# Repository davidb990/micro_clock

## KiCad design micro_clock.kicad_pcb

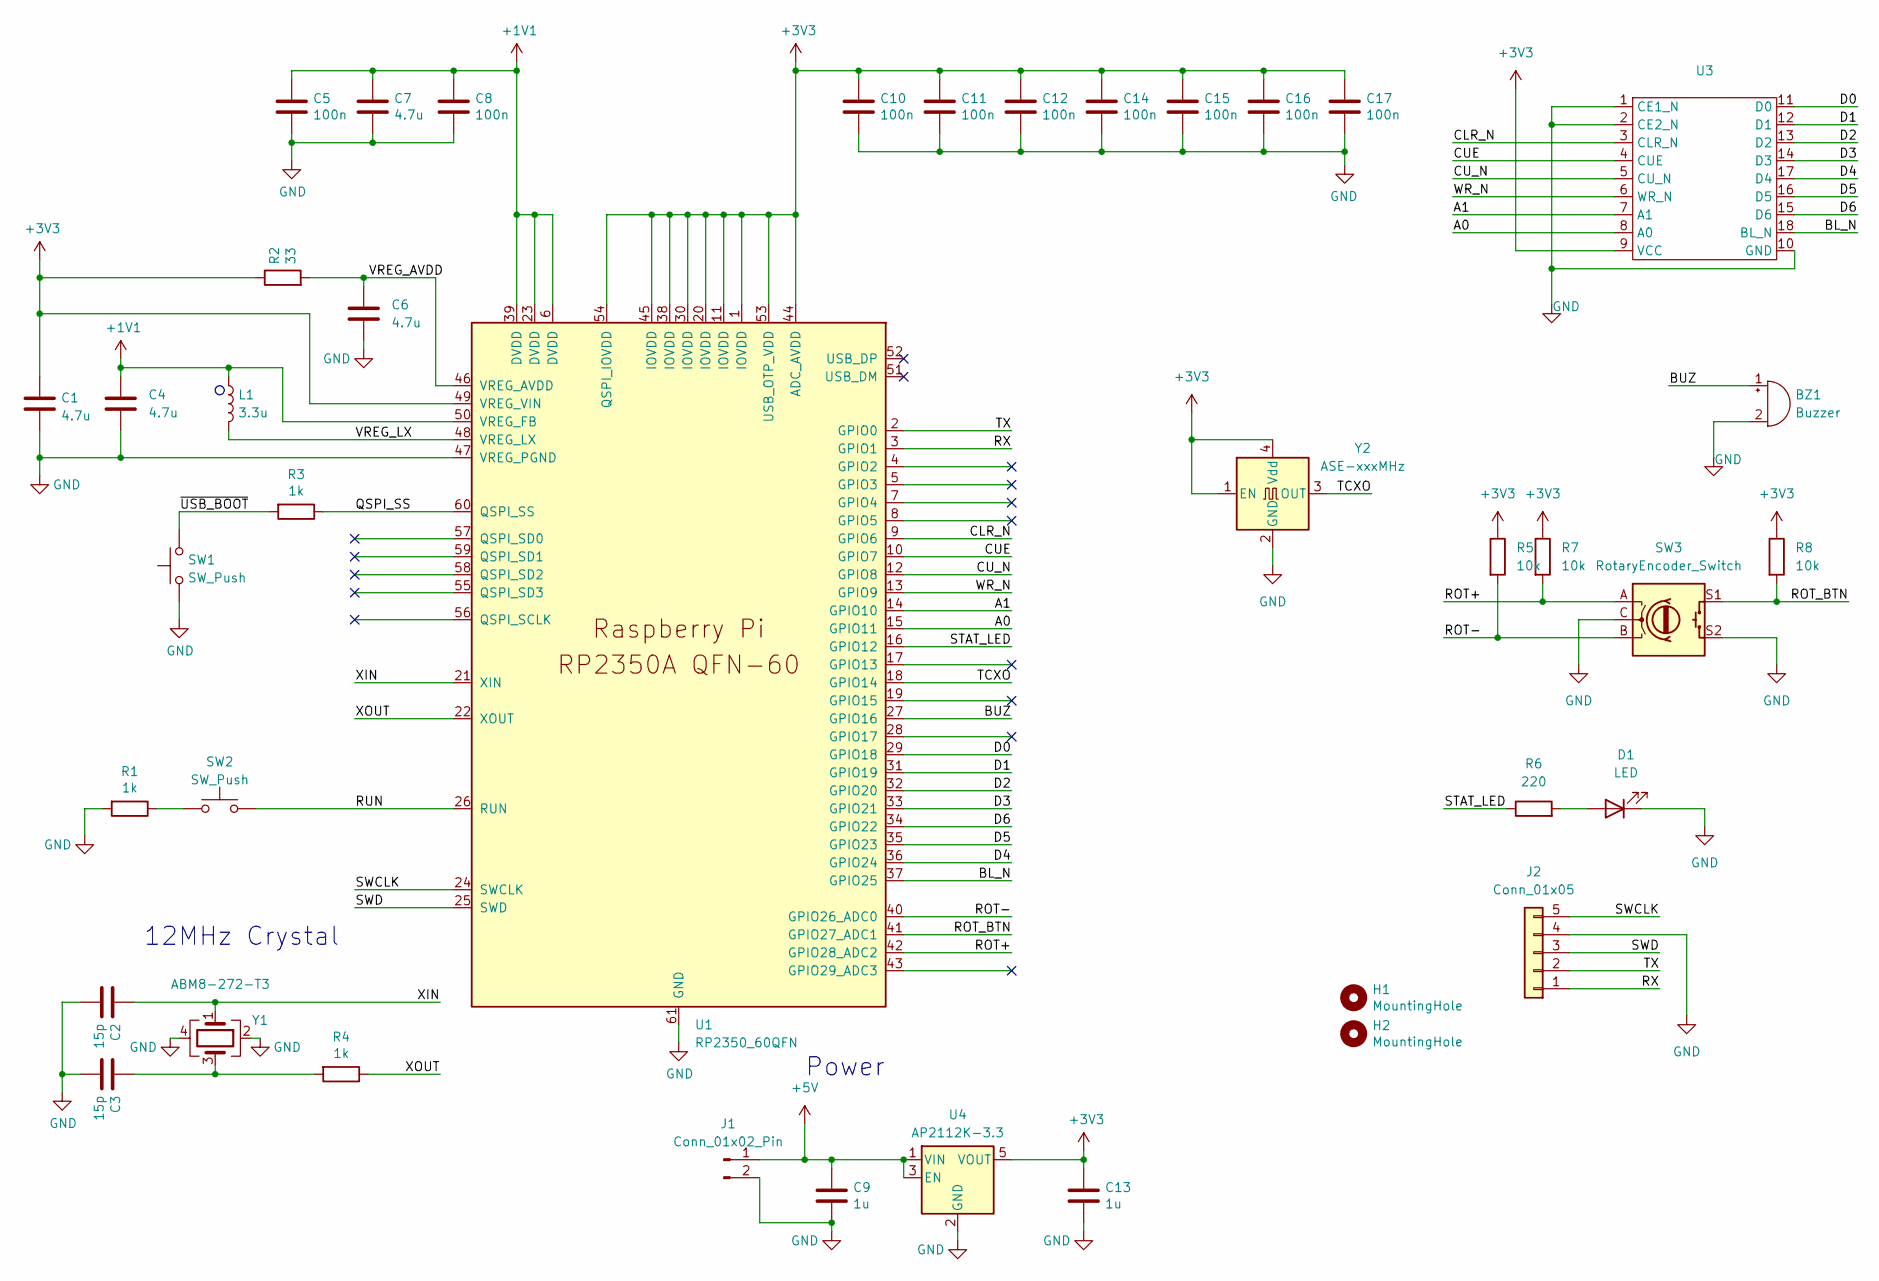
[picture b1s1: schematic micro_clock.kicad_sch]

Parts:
BZ1: Buzzer; PinHeader_1x02_P1.27mm_Vertical
C1, C4: 4.7u; C_0402_1005Metric_small_pads
C2, C3: 15p; C_0402_1005Metric
C5, C8, C10, C11, C12, C14, C15, C16, C17: 100n; C_0402_1005Metric
C6, C7: 4.7u; C_0402_1005Metric
C9, C13: 1u; C_0805_2012Metric
D1: LED; LED_D3.0mm
H1, H2: MountingHole; MountingHole_2.1mm
J1: Conn_01x02_Pin; PinHeader_1x02_P2.54mm_Vertical
J2: Conn_01x05; PinHeader_1x05_P2.54mm_Vertical
L1: 3.3u; L_pol_2016
R1, R3, R4: 1k; R_0402_1005Metric
R2: 33; R_0402_1005Metric
R5, R7, R8: 10k; R_0402_1005Metric
R6: 220; R_0402_1005Metric
SW1, SW2: SW_Push; SW_Push_1P1T_NO_Vertical_Wuerth_434133025816
SW3: RotaryEncoder_Switch; rot_encode
U1: RP2350_60QFN; RP2350-QFN-60-1EP_7x7_P0.4mm_EP3.4x3.4mm_ThermalVias
U3: DL2416
U4: AP2112K-3.3; SOT-23-5
Y1: ABM8-272-T3; Crystal_SMD_3225-4Pin_3.2x2.5mm
Y2: ASE-xxxMHz; Oscillator_SMD_Abracon_ASE-4Pin_3.2x2.5mm

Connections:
+1V1: C4.1, C5.1, C7.1, C8.1, L1.1, U1.6 (DVDD), U1.23 (DVDD), U1.39 (DVDD), U1.50 (VREG_FB)
+3V3: C1.1, C10.1, C11.1, C12.1, C13.1, C14.1, C15.1, C16.1, C17.1, R2.1, R5.1, R7.1, R8.1, U1.1 (IOVDD), U1.11 (IOVDD), U1.20 (IOVDD), U1.30 (IOVDD), U1.38 (IOVDD), U1.44 (ADC_AVDD), U1.45 (IOVDD), U1.49 (VREG_VIN), U1.53 (USB_OTP_VDD), U1.54 (QSPI_IOVDD), U3.9 (VCC), U4.5 (VOUT), Y2.1 (EN), Y2.4 (Vdd)
+5V: C9.1, J1.1, U4.1 (VIN), U4.3 (EN)
/A0: U1.15 (GPIO11), U3.8 (A0)
/A1: U1.14 (GPIO10), U3.7 (A1)
/BL_N: U1.37 (GPIO25), U3.18 (BL_N)
/BUZ: BZ1.1 (+), U1.27 (GPIO16)
/CLR_N: U1.9 (GPIO6), U3.3 (CLR_N)
/CUE: U1.10 (GPIO7), U3.4 (CUE)
/CU_N: U1.12 (GPIO8), U3.5 (CU_N)
/D0: U1.29 (GPIO18), U3.11 (D0)
/D1: U1.31 (GPIO19), U3.12 (D1)
/D2: U1.32 (GPIO20), U3.13 (D2)
/D3: U1.33 (GPIO21), U3.14 (D3)
/D4: U1.36 (GPIO24), U3.17 (D4)
/D5: U1.35 (GPIO23), U3.16 (D5)
/D6: U1.34 (GPIO22), U3.15 (D6)
/QSPI_SS: R3.1, U1.60 (QSPI_SS)
/ROT+: R7.2, SW3.A, U1.42 (GPIO28_ADC2)
/ROT-: R5.2, SW3.B, U1.40 (GPIO26_ADC0)
/ROT_BTN: R8.2, SW3.S1, U1.41 (GPIO27_ADC1)
/RUN: SW2.2, U1.26 (RUN)
/RX: J2.1, U1.3 (GPIO1)
/STAT_LED: R6.1, U1.16 (GPIO12)
/SWCLK: J2.5, U1.24 (SWCLK)
/SWD: J2.3, U1.25 (SWD)
/TCXO: U1.18 (GPIO14), Y2.3 (OUT)
/TX: J2.2, U1.2 (GPIO0)
/VREG_AVDD: C6.1, R2.2, U1.46 (VREG_AVDD)
/VREG_LX: L1.2, U1.48 (VREG_LX)
/WR_N: U1.13 (GPIO9), U3.6 (WR_N)
/XIN: C2.1, U1.21 (XIN), Y1.1
/XOUT: R4.1, U1.22 (XOUT)
/~USB_BOOT: R3.2, SW1.2
GND: BZ1.2 (-), C1.2, C2.2, C3.2, C4.2, C5.2, C6.2, C7.2, C8.2, C9.2, C10.2, C11.2, C12.2, C13.2, C14.2, C15.2, C16.2, C17.2, D1.1 (K), J1.2, J2.4, R1.2, SW1.1, SW3.C, SW3.S2, U1.47 (VREG_PGND), U1.61 (GND), U3.1 (CE1_N), U3.2 (CE2_N), U3.10 (GND), U4.2 (GND), Y1.2, Y1.4, Y2.2 (GND)
unnamed: C3.1, R4.2, Y1.3
unnamed: D1.2 (A), R6.2
unnamed: R1.1, SW2.1

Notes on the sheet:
12MHz Crystal
Power

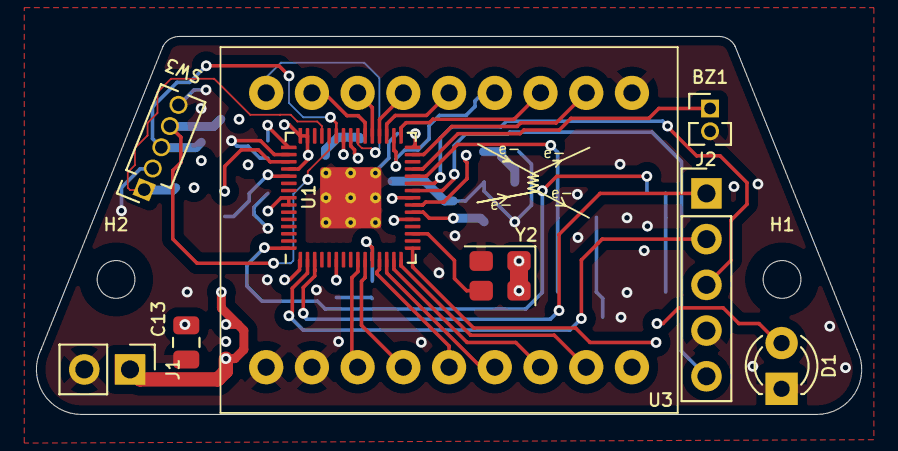
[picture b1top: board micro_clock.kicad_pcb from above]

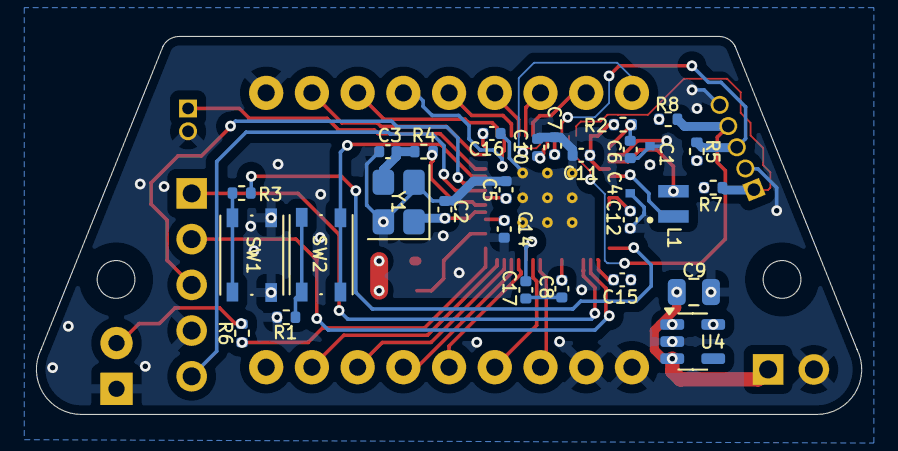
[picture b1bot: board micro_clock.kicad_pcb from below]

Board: 6 copper layers, 45.8 x 21.0 mm, 40 parts (29 on the bottom side), 38 nets.

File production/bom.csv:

Designator,Footprint,Quantity,Value,LCSC Part #
BZ1,PinHeader_1x02_P1.27mm_Vertical,1,Buzzer,
"C1, C4, C6, C7",0402,4,4.7u,
"C10, C11, C12, C14, C15, C16, C17, C5, C8",0402,9,100n,
"C13, C9",0805,2,1u,
"C2, C3",0402,2,15p,
D1,LED_D3.0mm,1,LED,
"H1, H2",MountingHole_2.1mm,2,MountingHole,
J1,PinHeader_1x02_P2.54mm_Vertical,1,Conn_01x02_Pin,
J2,PinHeader_1x05_P2.54mm_Vertical,1,Conn_01x05,
L1,L_pol_2016,1,3.3u,
"R1, R3, R4",0402,3,1k,
R2,0402,1,33,
"R5, R7, R8",0402,3,10k,
R6,0402,1,220,
"SW1, SW2",SW_Push_1P1T_NO_Vertical_Wuerth_434133025816,2,SW_Push,
SW3,rot_encode,1,RotaryEncoder_Switch,
U1,RP2350-QFN-60-1EP_7x7_P0.4mm_EP3.4x3.4mm_ThermalVias,1,RP2350_60QFN,
U3,DL2416,1,~,
U4,SOT-23-5,1,AP2112K-3.3,
Y1,Crystal_SMD_3225-4Pin_3.2x2.5mm,1,ABM8-272-T3,
Y2,Oscillator_SMD_Abracon_ASE-4Pin_3.2x2.5mm,1,ASE-xxxMHz,

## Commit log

2025-09-30 init
2025-09-30 adding kicad files
2025-09-30 adding git ignore
2025-09-30 gitignore update
2025-09-30 moving step to its own dir
2025-09-30 git ignore the production backups
